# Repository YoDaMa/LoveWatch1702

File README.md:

# LoveWatch 1702

### ELEC 327 Final Project
### Yoseph Maguire, Yovahn Hoole, Chandler Burke

## Abstract

Love Watch 1702 is a smart watch capable of measuring heart rate, oxygen saturation and most importantly the presence of loovvee. We three members of the Lonely Hearts Club, Yoseph Maguire, Yovahn Hoole and Chandler Burke have come up with a unique and state of the art system to help a user detect if they are in love by detecting a spike in heart rate. This research has far reaching consequences in protecting young ELECs from the distractions of college life.  

## Final Product

After pivoting drastically due to the failure of the I2C MSP430 Library we wrote, among other things, we ended up with a design based on an Arduino. Represented in breadboard version, the system uses I2C to read infrared values from the MAX30105 sensor, and then after using those values to calculate heart rate, send back graphical representations of heart rate to the 14-Segment Display. To model a simple threshold algorithm, if the user heart rate exceeds 80 BPM, it triggers a “Love” animation, indicating to the user that they have the potential to be in love (note, this system has an extremely high false positive rate).

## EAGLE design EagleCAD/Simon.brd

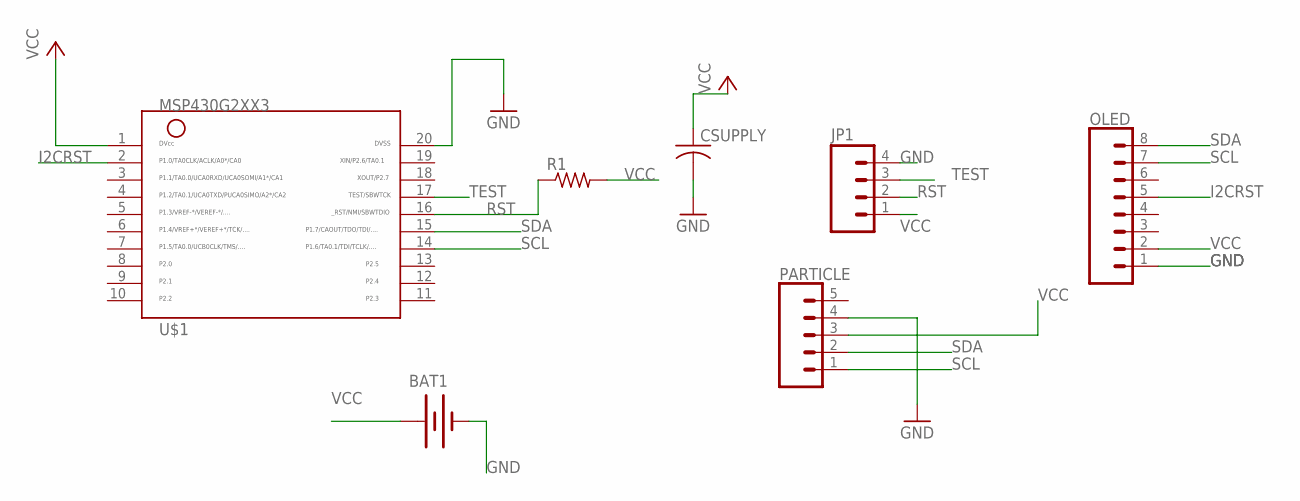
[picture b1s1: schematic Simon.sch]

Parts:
BAT1: BATTERYBU2032SM; BU2032SM
CSUPPLY: C-USC1206; C1206
JP1: M04LOCK; 1X04_LOCK
OLED: CONN_08"; 1X08
PARTICLE: CONN_05; 1X05
R1: R-US_R1206; R1206
U$1: MSP430G2XX3TSSOP; PW20

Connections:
GND: BAT1.P$2 (-), CSUPPLY.2, JP1.4, OLED.1, PARTICLE.4, U$1.20
I2CRST: OLED.5, U$1.2
RST: JP1.2, R1.1, U$1.16
SCL: OLED.7, PARTICLE.1, U$1.14
SDA: OLED.8, PARTICLE.2, U$1.15
TEST: JP1.3, U$1.17
VCC: BAT1.P$1 (+), CSUPPLY.1, JP1.1, OLED.2, PARTICLE.3, R1.2, U$1.1

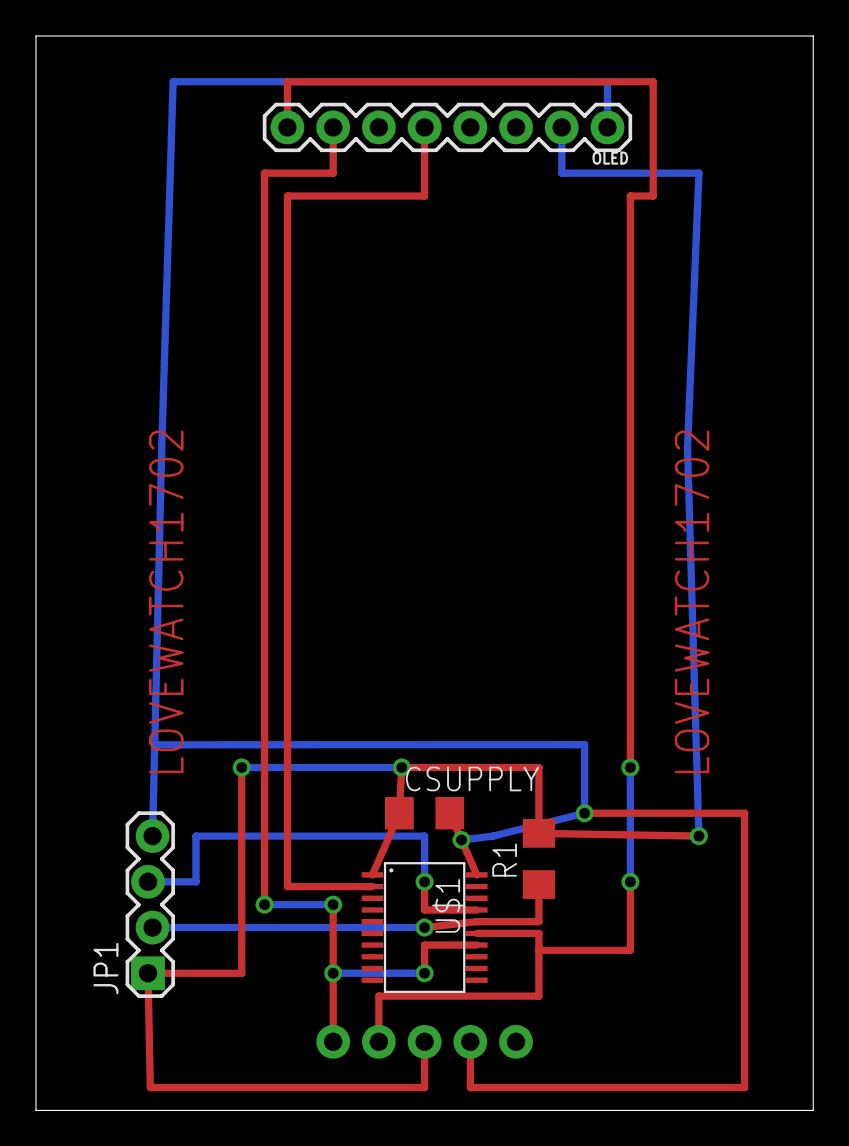
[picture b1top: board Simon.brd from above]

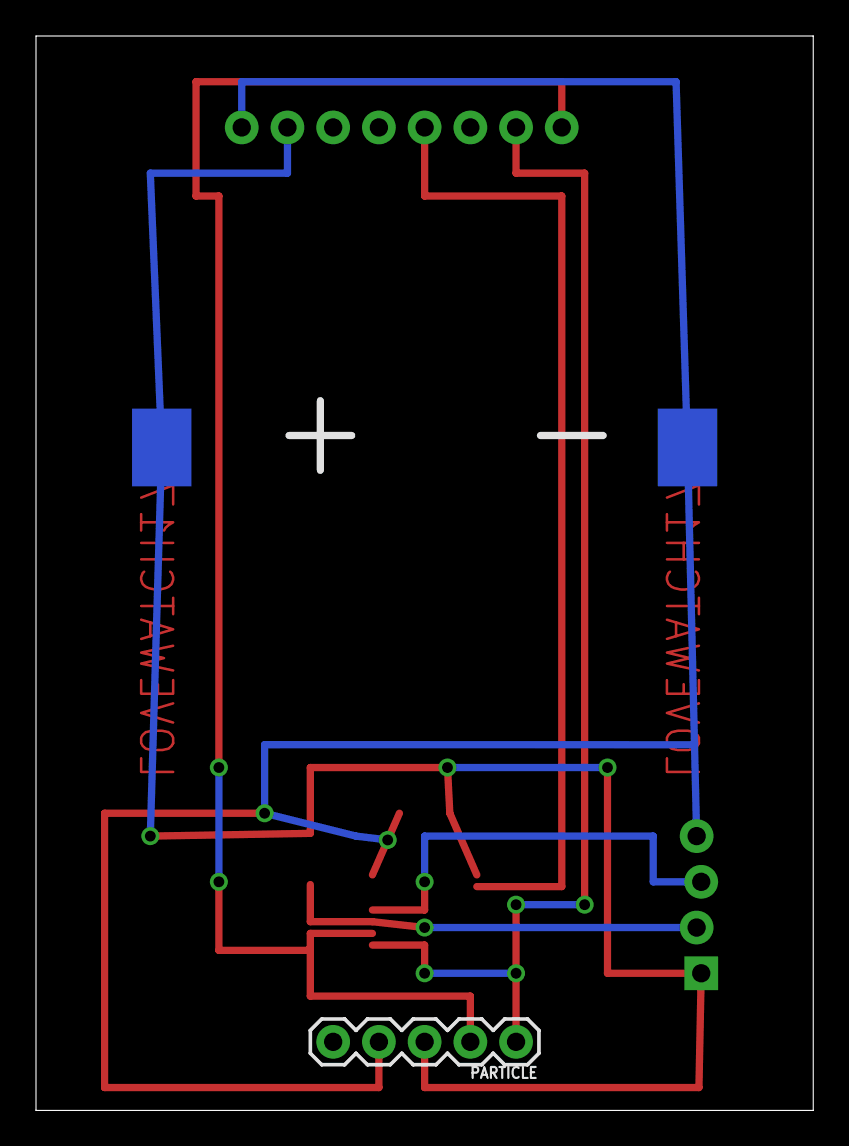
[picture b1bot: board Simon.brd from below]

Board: 2 copper layers, 43.2 x 59.7 mm, 7 parts (2 on the bottom side), 7 nets.

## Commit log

2017-05-04 Final for ELEC 327
    Love Watch is just a simple heart rate monitor
2017-05-04 Created Readme
2017-05-04 Writeup
2017-05-05 Update 21:11
2017-05-05 clean
2017-05-05 added docs
2017-05-05 Set theme jekyll-theme-cayman
2017-05-05 Added Report to index.md
2017-05-05 imgs
2017-05-05 Update ReadMe.md
    Matches website
2017-05-05 Update index.md
    fixed pics
2017-05-05 fixed imgs
2017-05-05 Minimal ReadMe.md
2017-05-05 imgfix
2017-05-05 yaktest
2017-05-05 rawcontent
2017-05-05 pic finish
2017-05-05 Added presentation
2017-05-05 embed videos
2017-05-05 update video url

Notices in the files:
parts and their libraries:
SparkFun: Licensing: CC v3.0 Share-Alike You are welcome to use this library for commercial purposes.
SparkFun-Connectors: Licensing: Creative Commons ShareAlike 4.0 International - https://creativecommons.org/licenses/by-sa/4.0
